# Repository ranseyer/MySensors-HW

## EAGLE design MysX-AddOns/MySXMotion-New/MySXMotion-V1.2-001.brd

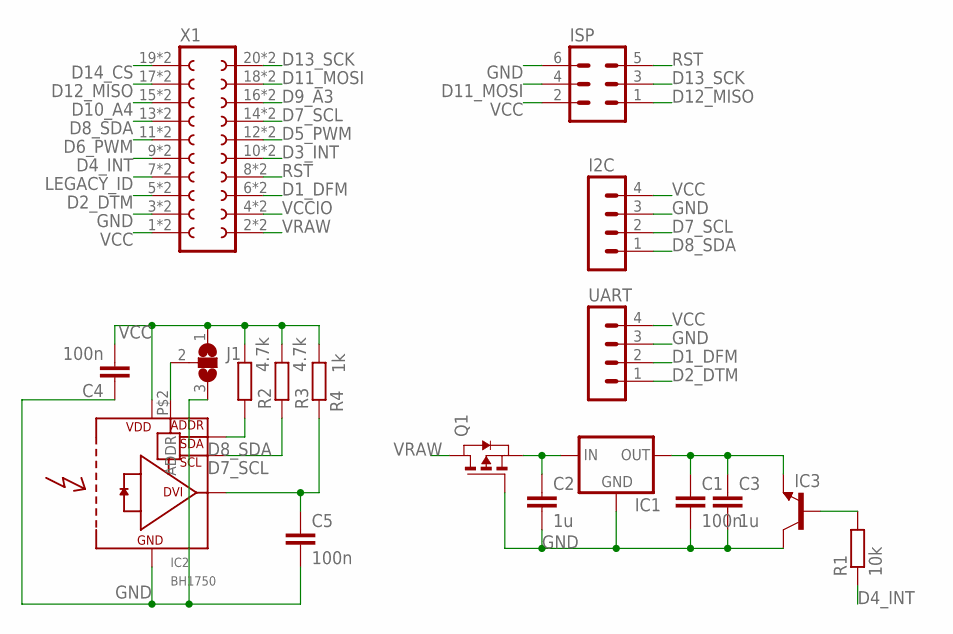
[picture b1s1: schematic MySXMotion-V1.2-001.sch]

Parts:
C1, C4, C5: 100n; C0603
C2: 1u; C0603
C3: 1u; C0805
I2C: MA04-1
IC1: XC63FPM; SOT23
IC2: BH1750; WSOF6
IC3: -NPN-TO5; TO5
ISP: MA03-2
J1: SJ2W; SJ_2
Q1: PMOSSOT23; SOT-23
R1: 10k; R0603
R2, R3: 4.7k; R0603
R4: 1k; R0603
UART: MA04-1
X1: FE10-2

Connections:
D1_DFM: UART.2, X1.6, X1.P$6 (6)
D2_DTM: UART.1, X1.5, X1.P$5 (5)
D3_INT: X1.10, X1.P$10 (10)
D4_INT: R1.1, X1.9, X1.P$9 (9)
D5_PWM: X1.12, X1.P$12 (12)
D6_PWM: X1.11, X1.P$11 (11)
D7_SCL: I2C.2, IC2.P$6 (SCL), R3.1, X1.14, X1.P$14 (14)
D8_SDA: I2C.1, IC2.P$4 (SDA), R2.1, X1.13, X1.P$13 (13)
D9_A3: X1.16, X1.P$16 (16)
D10_A4: X1.15, X1.P$15 (15)
D11_MOSI: ISP.4, X1.18, X1.P$18 (18)
D12_MISO: ISP.1, X1.17, X1.P$17 (17)
D13_SCK: ISP.3, X1.20, X1.P$20 (20)
D14_CS: X1.19, X1.P$19 (19)
GND: C1.2, C2.2, C3.2, C4.1, C5.2, I2C.3, IC1.1 (GND), IC2.P$3 (GND), IC3.3 (C), ISP.6, J1.3, Q1.3 (G), UART.3, X1.3, X1.P$3 (3)
LEGACY_ID: X1.7, X1.P$7 (7)
unnamed: C5.1, IC2.P$5 (DVI), R4.2
unnamed: IC2.P$2 (ADDR), J1.2
unnamed: IC3.2 (B), R1.2
unnamed: C2.1, IC1.3 (IN), Q1.2 (S)
unnamed: C1.1, C3.1, IC1.2 (OUT), IC3.1 (E)
RST: ISP.5, X1.8, X1.P$8 (8)
VCC: C4.2, I2C.4, IC2.P$1 (VCC), ISP.2, J1.1, R2.2, R3.2, R4.1, UART.4, X1.1, X1.P$1 (1)
VCCIO: X1.4, X1.P$4 (4)
VRAW: Q1.1 (D), X1.2, X1.P$2 (2)

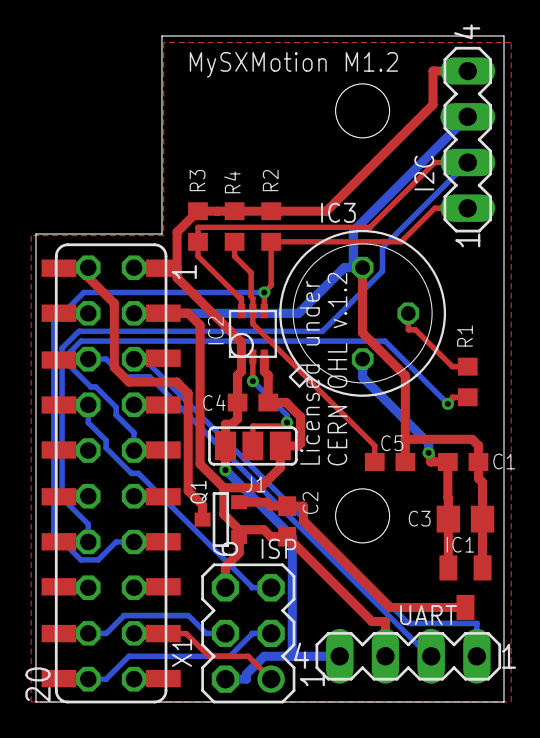
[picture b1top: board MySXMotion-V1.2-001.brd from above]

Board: 2 copper layers, 26.0 x 37.0 mm, 18 parts (0 on the bottom side), 25 nets.

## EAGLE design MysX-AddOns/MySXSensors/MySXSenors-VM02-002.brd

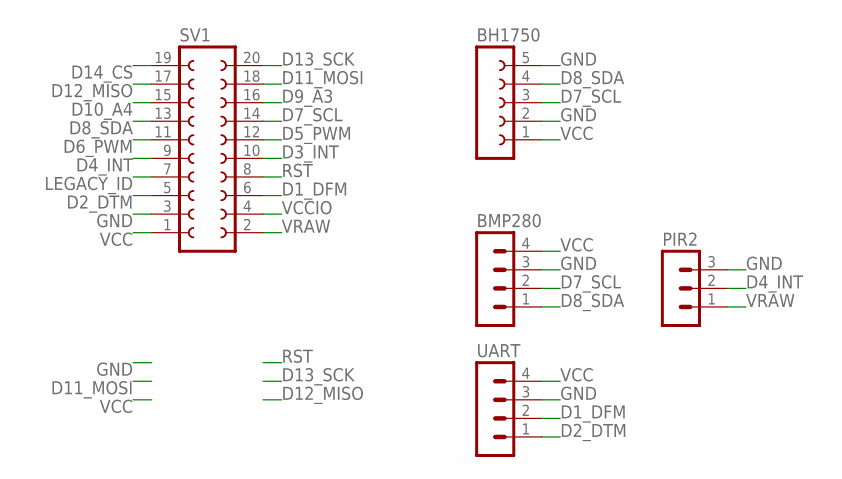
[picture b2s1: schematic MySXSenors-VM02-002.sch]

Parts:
BH1750: FE05-1
BMP280: MA04-1
PIR2: MA03-1
SV1: FE10-2
UART: MA04-1

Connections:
D1_DFM: SV1.6, UART.2
D2_DTM: SV1.5, UART.1
D3_INT: SV1.10
D4_INT: PIR2.2, SV1.9
D5_PWM: SV1.12
D6_PWM: SV1.11
D7_SCL: BH1750.3, BMP280.2, SV1.14
D8_SDA: BH1750.4, BMP280.1, SV1.13
D9_A3: SV1.16
D10_A4: SV1.15
D11_MOSI: SV1.18
D12_MISO: SV1.17
D13_SCK: SV1.20
D14_CS: SV1.19
GND: BH1750.2, BH1750.5, BMP280.3, PIR2.3, SV1.3, UART.3
LEGACY_ID: SV1.7
RST: SV1.8
VCC: BH1750.1, BMP280.4, SV1.1, UART.4
VCCIO: SV1.4
VRAW: PIR2.1, SV1.2

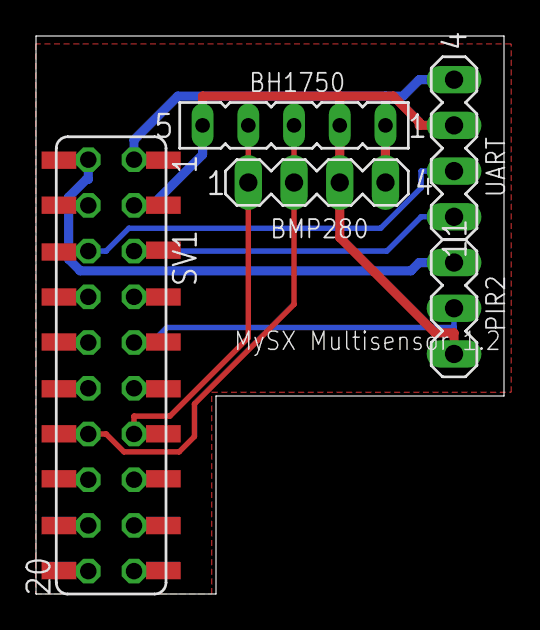
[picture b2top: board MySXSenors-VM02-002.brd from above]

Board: 2 copper layers, 26.0 x 31.0 mm, 5 parts (0 on the bottom side), 8 nets.

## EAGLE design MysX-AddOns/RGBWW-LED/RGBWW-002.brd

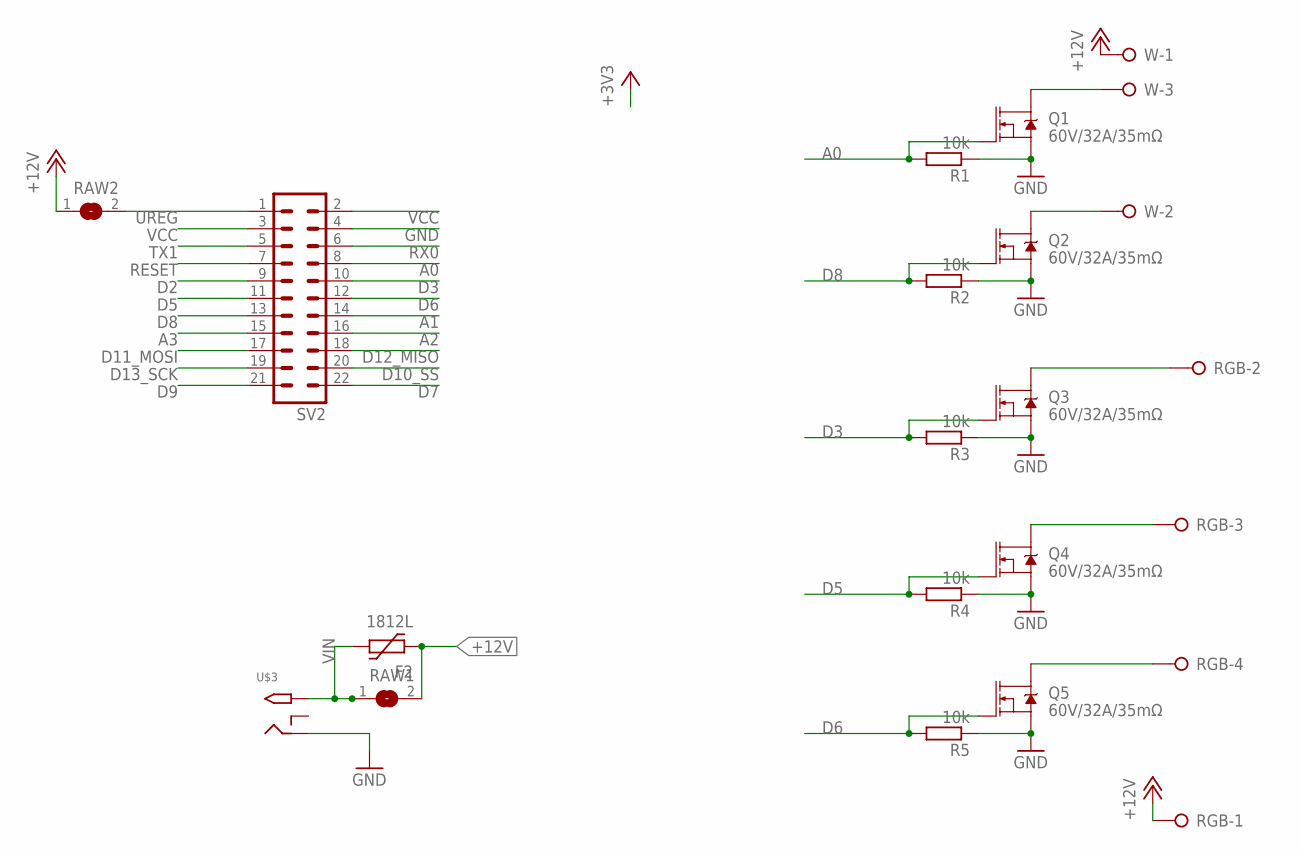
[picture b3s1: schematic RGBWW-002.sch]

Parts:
F2: 1812L
Q1, Q2, Q3, Q4, Q5: 60V/32A/35mΩ; TO220V
R1, R2, R3, R4, R5: 10k; R0805
RAW1, RAW2: SJ
RGB: W237-04P; W237-4P
SV2: MA11-2
U$3: 2.1MMJACKTHM; PJ-102A
W: W237-03P; W237-133

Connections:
+12V: F2.P$1 (1), RAW1.2, RAW2.1, RGB.1, W.1
A0: Q1.1 (G), R1.2, SV2.8
A1: SV2.14
A2: SV2.16
A3: SV2.15
D2: SV2.9
D3: Q3.1 (G), R3.2, SV2.10
D5: Q4.1 (G), R4.2, SV2.11
D6: Q5.1 (G), R5.2, SV2.12
D7: SV2.22
D8: Q2.1 (G), R2.2, SV2.13
D9: SV2.21
D10_SS: SV2.20
D11_MOSI: SV2.17
D12_MISO: SV2.18
D13_SCK: SV2.19
GND: Q1.3 (S), Q2.3 (S), Q3.3 (S), Q4.3 (S), Q5.3 (S), R1.1, R2.1, R3.1, R4.1, R5.1, SV2.4, U$3.RING
RESET: SV2.7
RGB-WW-OUT: Q1.2 (D), W.3
RGB-WW-OUT1: Q2.2 (D), W.2
RGB-WW-OUT2: Q3.2 (D), RGB.2
RGB-WW-OUT3: Q4.2 (D), RGB.3
RGB-WW-OUT4: Q5.2 (D), RGB.4
RX0: SV2.6
TX1: SV2.5
UREG: RAW2.2, SV2.1
VCC: SV2.2, SV2.3
VIN: F2.P$2 (2), RAW1.1, U$3.TIP

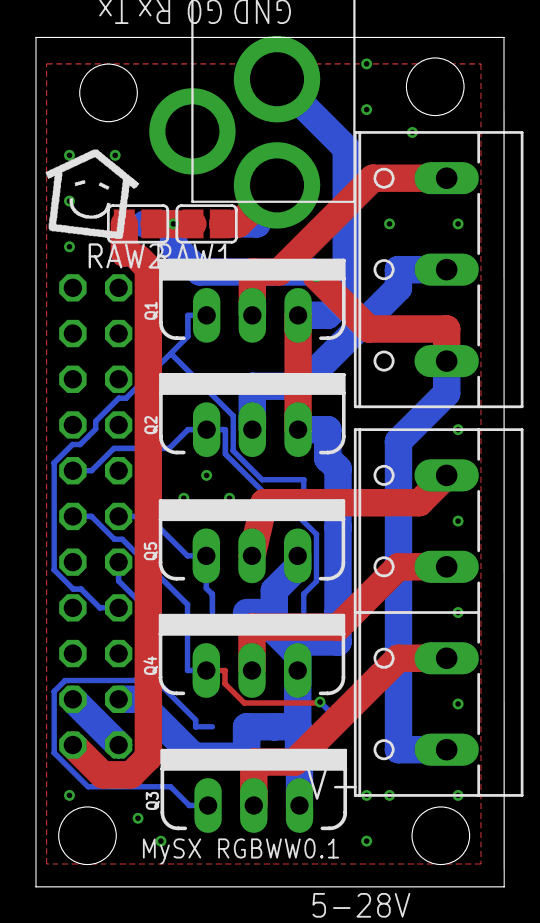
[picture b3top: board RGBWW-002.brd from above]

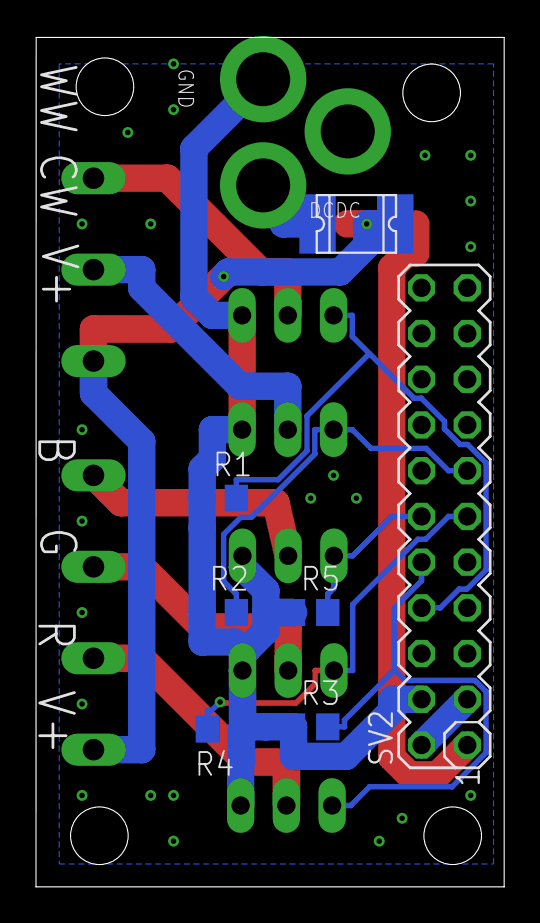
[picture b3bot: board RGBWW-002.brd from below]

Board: 2 copper layers, 26.0 x 47.2 mm, 18 parts (7 on the bottom side), 15 nets.

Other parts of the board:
U$2: LOGO

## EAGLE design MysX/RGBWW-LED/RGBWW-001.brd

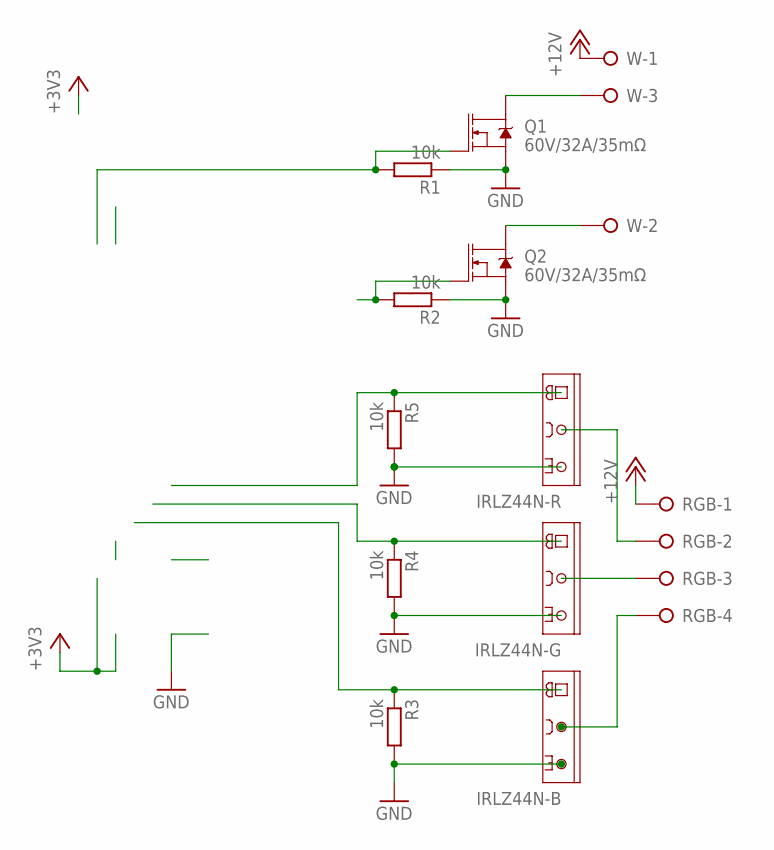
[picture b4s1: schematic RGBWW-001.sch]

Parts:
IRLZ44N-B, IRLZ44N-G, IRLZ44N-R: TIP121; TO220AV
Q1, Q2: 60V/32A/35mΩ; TO220V
R1, R2, R3, R4, R5: 10k; R0805
RGB: W237-04P; W237-4P
W: W237-03P; W237-133

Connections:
+12V: RGB.1, W.1
GND: IRLZ44N-B.E, IRLZ44N-G.E, IRLZ44N-R.E, Q1.3 (S), Q2.3 (S), R1.1, R2.1, R3.2, R4.2, R5.2
RGB-B: IRLZ44N-B.B, R3.1
RGB-B-OUT: IRLZ44N-B.C, RGB.4
RGB-G: IRLZ44N-G.B, R4.1
RGB-G-OUT: IRLZ44N-G.C, RGB.3
RGB-R: IRLZ44N-R.B, R5.1
RGB-R-OUT: IRLZ44N-R.C, RGB.2
RGB-WW: Q1.1 (G), R1.2
RGB-WW1: Q2.1 (G), R2.2
RGB-WW-OUT: W.3
RGB-WW-OUT1: W.2

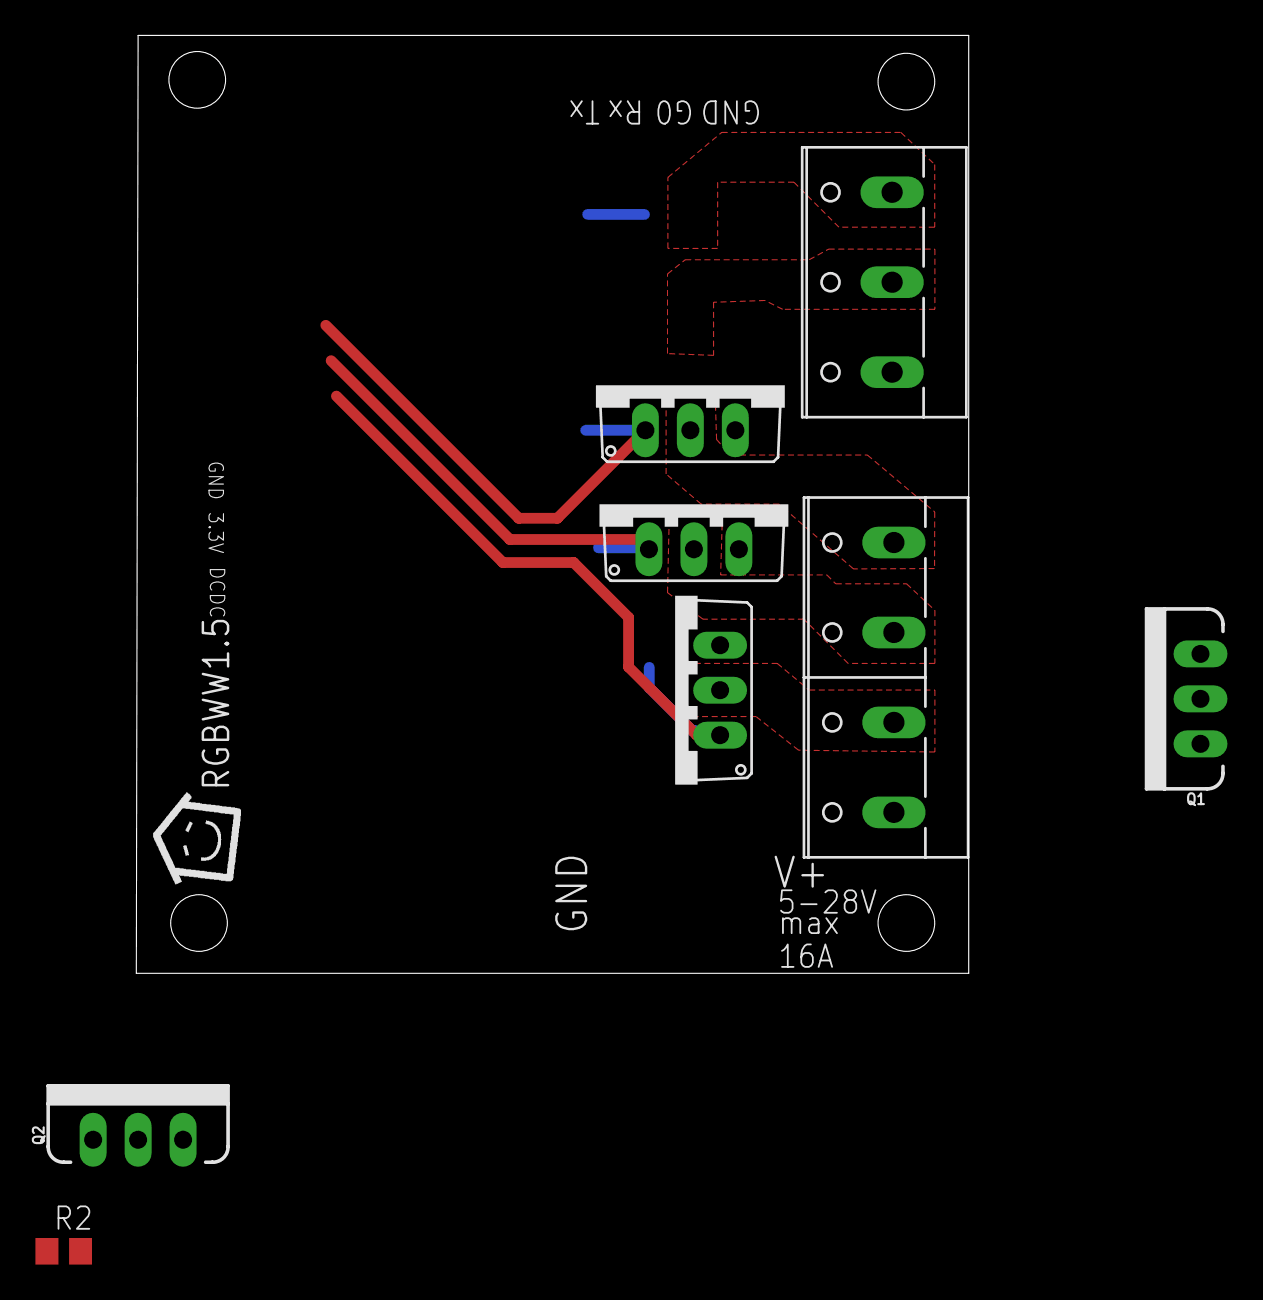
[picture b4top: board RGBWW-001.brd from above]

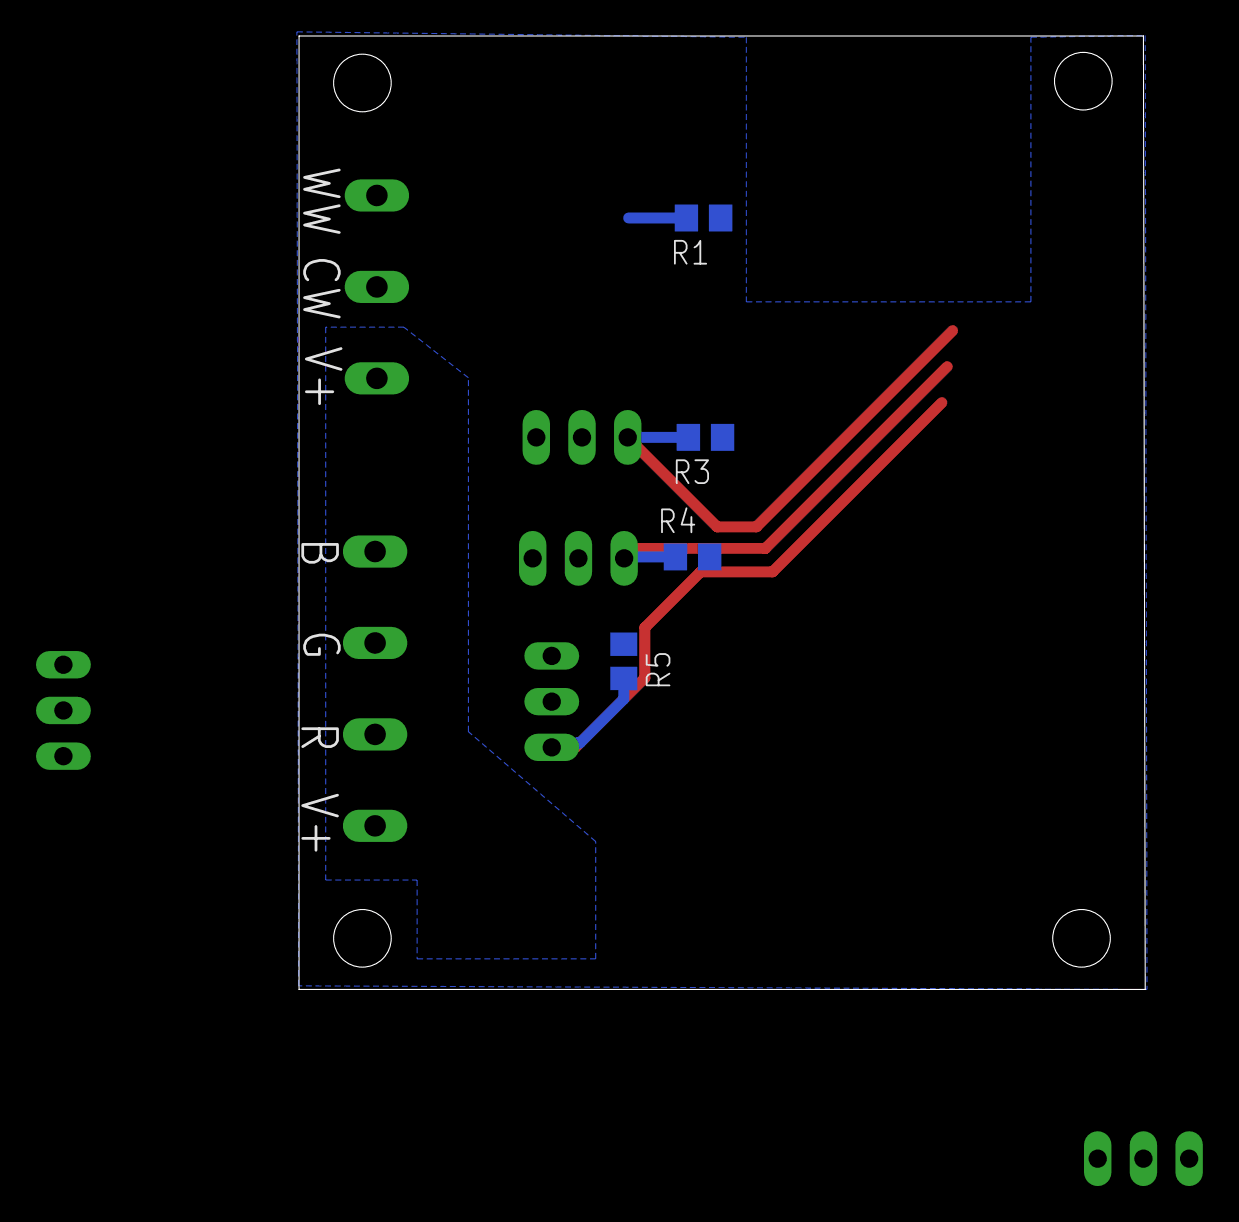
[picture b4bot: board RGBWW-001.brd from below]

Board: 2 copper layers, 47.0 x 53.0 mm, 13 parts (4 on the bottom side), 10 nets.

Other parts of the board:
U$1: LOGO

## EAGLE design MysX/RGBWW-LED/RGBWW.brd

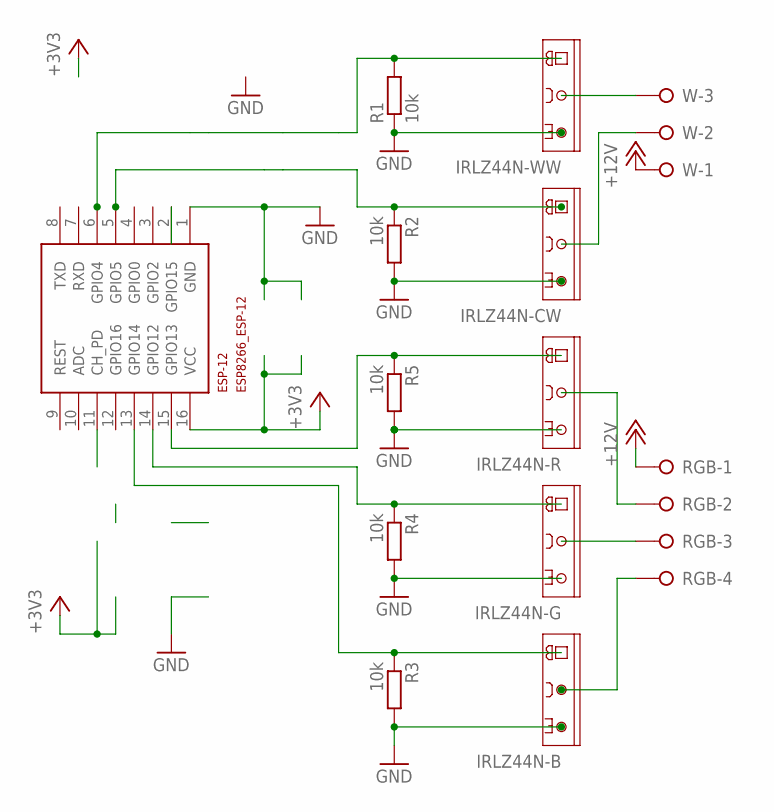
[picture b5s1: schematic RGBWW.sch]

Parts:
ESP-12: ESP8266_ESP-12; ESP8266-ESP12
IRLZ44N-B, IRLZ44N-CW, IRLZ44N-G, IRLZ44N-R, IRLZ44N-WW: TIP121; TO220AV
R1, R2, R3, R4, R5: 10k; R0805
RGB: W237-04P; W237-4P
W: W237-03P; W237-133

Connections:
+3V3: ESP-12.16 (VCC)
+12V: RGB.1, W.1
GND: ESP-12.1 (GND), IRLZ44N-B.E, IRLZ44N-CW.E, IRLZ44N-G.E, IRLZ44N-R.E, IRLZ44N-WW.E, R1.1, R2.2, R3.2, R4.2, R5.2
RGB-B: ESP-12.13 (GPIO14), IRLZ44N-B.B, R3.1
RGB-B-OUT: IRLZ44N-B.C, RGB.4
RGB-CW: ESP-12.5 (GPIO5), IRLZ44N-CW.B, R2.1
RGB-CW-OUT: IRLZ44N-CW.C, W.2
RGB-G: ESP-12.14 (GPIO12), IRLZ44N-G.B, R4.1
RGB-G-OUT: IRLZ44N-G.C, RGB.3
RGB-R: ESP-12.15 (GPIO13), IRLZ44N-R.B, R5.1
RGB-R-OUT: IRLZ44N-R.C, RGB.2
RGB-WW: ESP-12.6 (GPIO4), IRLZ44N-WW.B, R1.2
RGB-WW-OUT: IRLZ44N-WW.C, W.3

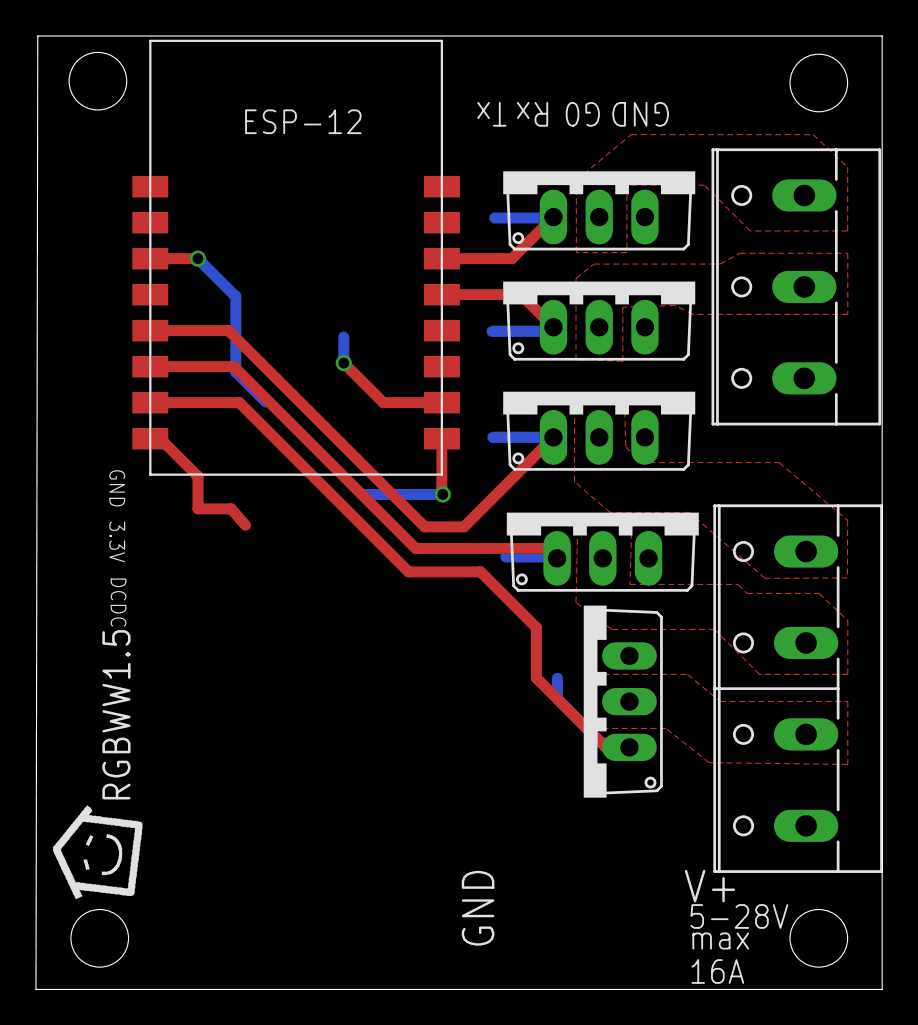
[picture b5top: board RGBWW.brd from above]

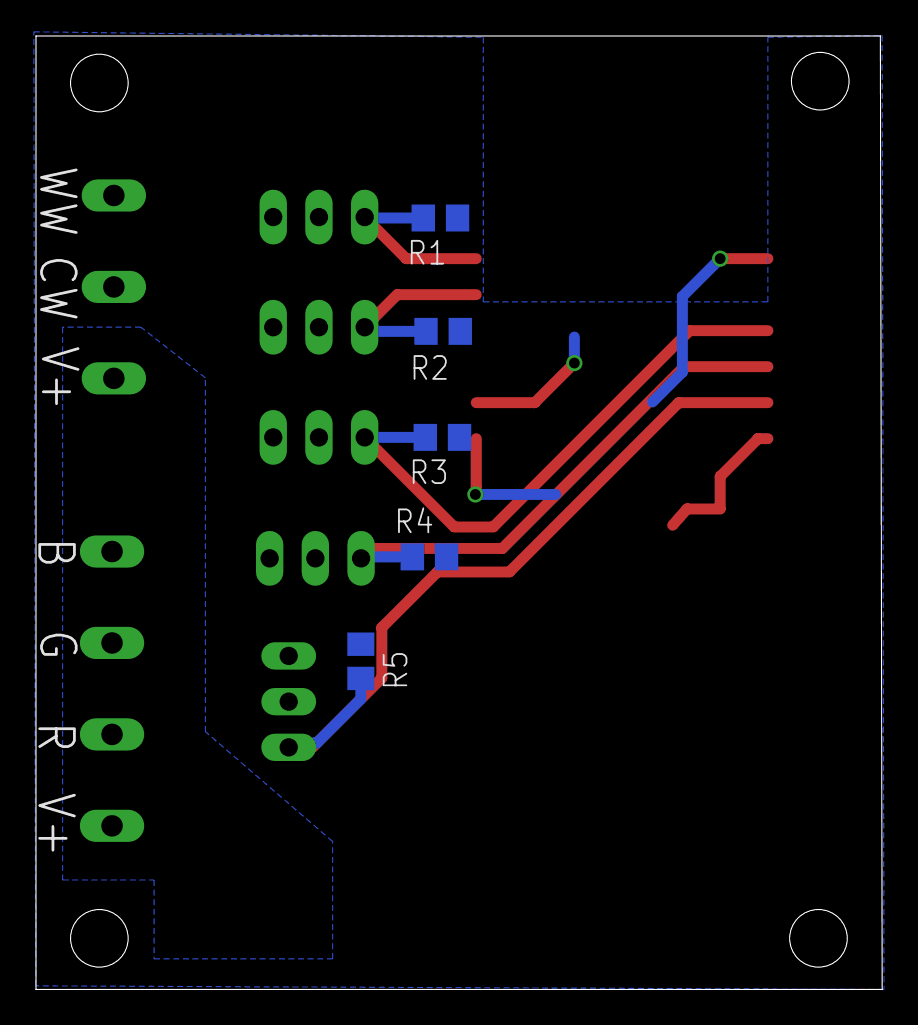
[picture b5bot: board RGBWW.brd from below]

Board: 2 copper layers, 47.0 x 53.0 mm, 14 parts (5 on the bottom side), 12 nets.

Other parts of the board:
U$1: LOGO

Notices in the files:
MysX-AddOns/MySXMotion-New/MySXMotion-V1.2-001.brd:
Licensed under
CERN OHL v.1.2
parts and their libraries:
SparkFun-DiscreteSemi: Licensing: Creative Commons ShareAlike 4.0 International - https://creativecommons.org/licenses/by-sa/4.0
